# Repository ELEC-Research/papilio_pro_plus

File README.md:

# Papilio Pro Plus

This is a KICAD implementation of the Papilio Pro including production files for JLCPCB.  The Papilio pro is no longer in production so you can use this to order one for yourself.

There are some changes:
* Built-in USB-C JTAG port

## Author

Phill Brown is the primary author. 

## Licence

This work is licenced under a creative commons licence, rather like the original papilio pro.

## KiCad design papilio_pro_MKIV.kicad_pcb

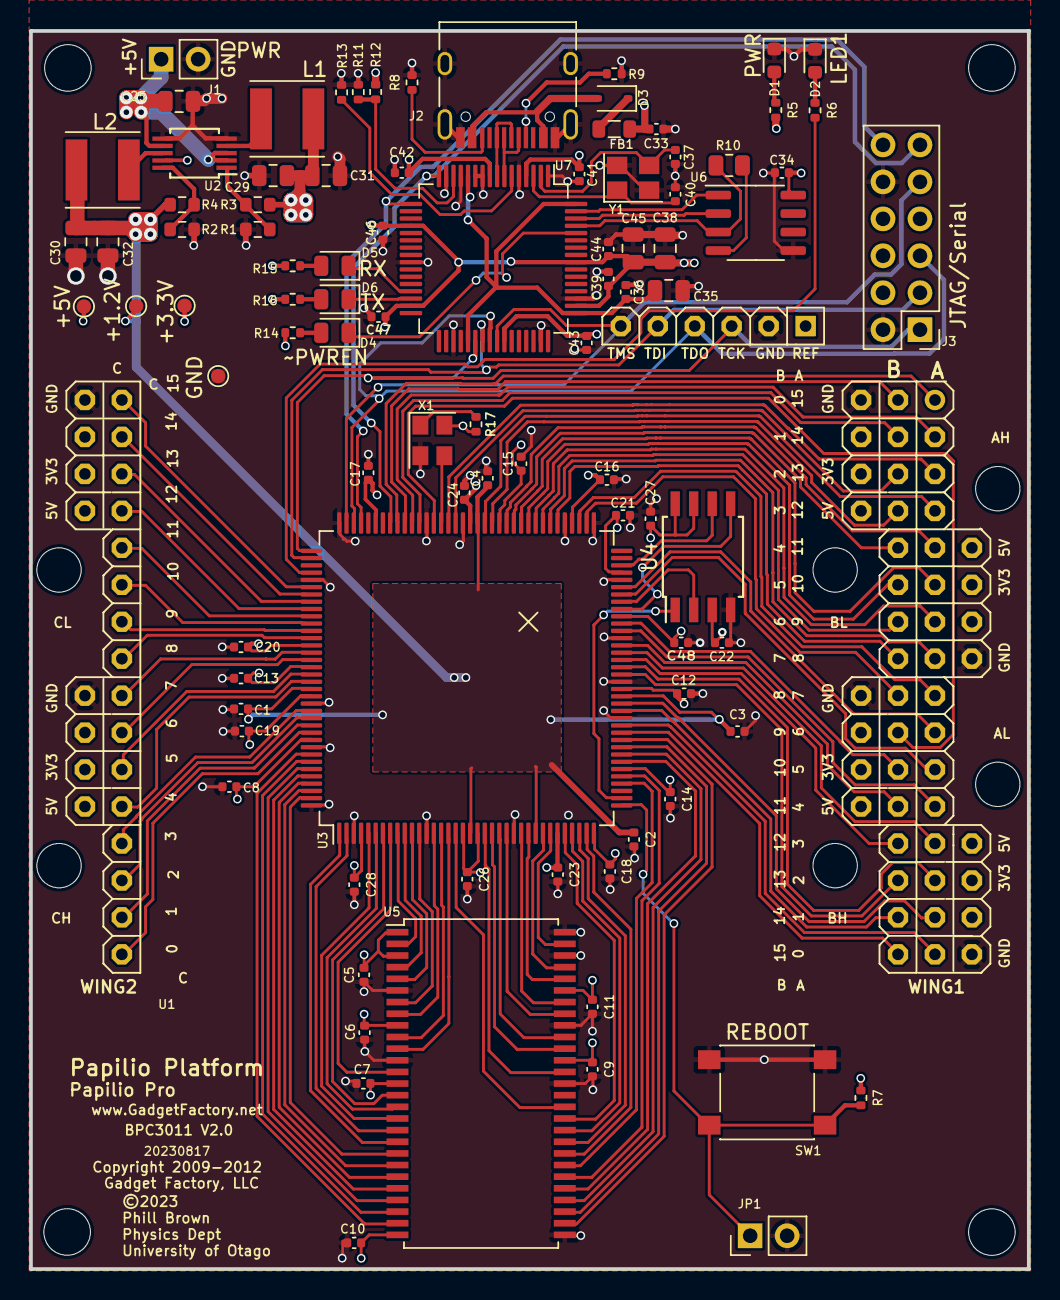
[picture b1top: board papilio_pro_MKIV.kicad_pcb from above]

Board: 4 copper layers, 68.6 x 85.1 mm, 96 parts (0 on the bottom side), 132 nets.

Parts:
C1, C2, C3, C4, C5, C6, C7, C8, C9, C10, C11, C12, C13, C14, C15, C16, C17, C18, C19, C20, C21, C22, C23, C24, C26, C27, C28, C48: .1uF; C_0402_1005Metric
C25: 10u/10V; C_0805_2012Metric
C29, C30, C31, C32: 10u/6V3; C_0805_2012Metric
C33, C34, C36, C39, C41, C42, C43, C44, C46, C47: 0.1; C_0402_1005Metric
C35: 3.3; C_0805_2012Metric
C37, C40: 27p; C_0402_1005Metric
C38, C45: 4.7; C_0805_2012Metric
D1: PWR; LED_0603_1608Metric
D2: LED1; LED_0603_1608Metric
D3: SD103AWS; D_SOD-323
D4: ~PWREN; LED_0805_2012Metric
D5: RX; LED_0805_2012Metric
D6: TX; LED_0805_2012Metric
FB1: 600 ohm; L_0805_2012Metric
H1, H2, H3, H4: MountingHole; MountingHole_3.2mm_M3
J1: PWR; PinHeader_1x02_P2.54mm_Vertical
J2: USB_C_Receptacle_USB2.0; USB_C_Receptacle_HRO_TYPE-C-31-M-12
J3: JTAG/Serial; PinHeader_2x06_P2.54mm_Vertical
JP1: JP1E; PinHeader_1x02_P2.54mm_Vertical
L1, L2: 3.3uH; L_Taiyo-Yuden_MD-5050
R1, R2, R4: 1.5K 1%; R_0603_1608Metric
R3: 6K8 1%; R_0603_1608Metric
R5: 1K8; R_0402_1005Metric
R6: 390; R_0402_1005Metric
R7: 47K; R_0402_1005Metric
R8, R9: 5.1k; R_0402_1005Metric
R10: 2.2k; R_0805_2012Metric
R11, R17: 10k; R_0402_1005Metric
R12: 4k7; R_0402_1005Metric
R13: 12k; R_0402_1005Metric
R14, R15, R16: 470; R_0402_1005Metric
SW1: REBOOT; SW_SPST_PTS645
TP1: +3.3V; TestPoint_Pad_D1.0mm
TP2: +1.2V; TestPoint_Pad_D1.0mm
TP3: +5V; TestPoint_Pad_D1.0mm
TP4: GND; TestPoint_Pad_D1.0mm
U1: Papilio Pro; COCOON_48BIT
U2: LTC3419MS; MSOP-10_3x3mm_P0.5mm
U3: XC6SLX9-TQG144; LQFP-144_20x20mm_P0.5mm
U4: 25CSM04xxSN; SOIC-8W_5.3x5.3mm_P1.27mm
U5: MT48LC16M16A2P; TSOP-II-54_22.2x10.16mm_P0.8mm
U6: 93LCxxB; SO-8_3.9x4.9mm_P1.27mm
U7: FT2232HL; LQFP-64_10x10mm_P0.5mm
X1: 3.2X2.5 32MHz Osc; Oscillator_SMD_Abracon_ASE-4Pin_3.2x2.5mm
Y1: 12MHz; Crystal_SMD_3225-4Pin_3.2x2.5mm

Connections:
+1V2: C1.1, C2.1, C3.1, C4.1, C30.1, C32.1, L2.2, R4.2, TP2.1, U3.19 (VCCINT), U3.28 (VCCINT), U3.52 (VCCINT), U3.89 (VCCINT), U3.128 (VCCINT)
+1V8: C35.1, C36.1, U7.12 (VCORE), U7.37 (VCORE), U7.49 (VREGOUT), U7.64 (VCORE)
+3.3V: C5.1, C6.1, C7.1, C8.1, C9.1, C10.1, C11.1, C12.1, C13.1, C14.1, C15.1, C16.1, C17.1, C18.1, C19.1, C20.1, C21.1, C22.1, C23.1, C24.1, C26.1, C27.1, C28.1, C29.1, C31.1, C34.1, C38.1, C39.1, C41.1, C42.1, C43.1, C44.1, C45.1, C46.1, C47.1, C48.1, J3.6, L1.2, R3.2, R7.1, R14.1, R15.1, R16.1, R17.1, TP1.1, U1.3 (3V3), U1.13 (3V3), U1.23 (3V3), U1.33 (3V3), U1.43 (3V3), U1.53 (3V3), U1.J1 (JTAG_REF), U2.9 (RUN2), U3.4 (VCCO_3), U3.18 (VCCO_3), U3.20 (VCCAUX), U3.31 (VCCO_3), U3.36 (VCCAUX), U3.42 (VCCO_2), U3.53 (VCCAUX), U3.63 (VCCO_2), U3.69 (IO_L1N_M0_CMPMISO_2), U3.76 (VCCO_1), U3.86 (VCCO_1), U3.90 (VCCAUX), U3.103 (VCCO_1), U3.122 (VCCO_0), U3.125 (VCCO_0), U3.129 (VCCAUX), U3.135 (VCCO_0), U4.3 (~WP), U4.7 (~HOLD), U4.8 (V_{CC}), U5.1 (VDD), U5.3 (VDDQ), U5.9 (VDDQ), U5.14 (VDD), U5.27 (VDD), U5.43 (VDDQ), U5.49 (VDDQ), U6.8 (VCC), U7.4 (VPHY), U7.9 (VPLL), U7.20 (VCCIO), U7.31 (VCCIO), U7.42 (VCCIO), U7.50 (VREGIN), U7.56 (VCCIO), X1.4 (Vdd)
+5V: C25.1, C33.1, FB1.1, J1.1, R5.2, R12.1, TP3.1, U1.4 (Vin), U1.14 (Vin), U1.24 (Vin), U1.34 (Vin), U1.44 (Vin), U1.54 (Vin), U2.2 (RUN1), U2.3 (MODE), U2.7 (VIN)
/Connectors/OSC_IN: U3.94 (IO_L40N_GCLK10_1), X1.3 (OUT)
/Connectors/W1_A1: U1.A0, U3.48 (IO_L48P_D7_2)
/Connectors/W1_A2: U1.A1, U3.51 (IO_L31P_GCLK31_D14_2)
/Connectors/W1_A3: U1.A2, U3.56 (IO_L30P_GCLK1_D13_2)
/Connectors/W1_A4: U1.A3, U3.58 (IO_L14P_D11_2)
/Connectors/W1_A5: U1.A4, U3.61 (IO_L12N_D2_MISO3_2)
/Connectors/W1_A6: U1.A5, U3.66 (IO_L2N_CMPMOSI_2)
/Connectors/W1_A7: U1.A6, U3.67 (IO_L2P_CMPCLK_2)
/Connectors/W1_A8: U1.A7, U3.75 (IO_L74P_AWAKE_1)
/Connectors/W1_A9: U1.A8, U3.79 (IO_L47P_1)
/Connectors/W1_A10: U1.A9, U3.81 (IO_L46P_1)
/Connectors/W1_A11: U1.A10, U3.83 (IO_L45P_1)
/Connectors/W1_A12: U1.A11, U3.85 (IO_L43P_GCLK5_1)
/Connectors/W1_A13: U1.A12, U3.88 (IO_L42P_GCLK7_1)
/Connectors/W1_A14: U1.A13, U3.93 (IO_L41P_GCLK9_IRDY1_1)
/Connectors/W1_A15: U1.A14, U3.98 (IO_L34P_1)
/Connectors/W1_A16: U1.A15, U3.100 (IO_L33P_1)
/Connectors/W1_B1: U1.B0, U3.99 (IO_L33N_1)
/Connectors/W1_B2: U1.B1, U3.97 (IO_L34N_1)
/Connectors/W1_B3: U1.B2, U3.92 (IO_L41N_GCLK8_1)
/Connectors/W1_B4: U1.B3, U3.87 (IO_L42N_GCLK6_TRDY1_1)
/Connectors/W1_B5: U1.B4, U3.84 (IO_L43N_GCLK4_1)
/Connectors/W1_B6: U1.B5, U3.82 (IO_L45N_1)
/Connectors/W1_B7: U1.B6, U3.80 (IO_L46N_1)
/Connectors/W1_B8: U1.B7, U3.78 (IO_L47N_1)
/Connectors/W1_B9: U1.B8, U3.74 (IO_L74N_DOUT_BUSY_1)
/Connectors/W1_B10: U1.B9, U3.95 (IO_L40P_GCLK11_1)
/Connectors/W1_B11: U1.B10, U3.62 (IO_L12P_D1_MISO2_2)
/Connectors/W1_B12: U1.B11, U3.59 (IO_L13N_D10_2)
/Connectors/W1_B13: U1.B12, U3.57 (IO_L14N_D12_2)
/Connectors/W1_B14: U1.B13, U3.55 (IO_L30N_GCLK0_USERCCLK_2)
/Connectors/W1_B15: U1.B14, U3.50 (IO_L31N_GCLK30_D15_2)
/Connectors/W1_B16: U1.B15, U3.47 (IO_L48N_RDWR_B_VREF_2)
/Connectors/W2_A1: U1.C15, U3.114 (IO_L65N_SCP2_0)
/Connectors/W2_A2: U1.C14, U3.115 (IO_L65P_SCP3_0)
/Connectors/W2_A3: U1.C13, U3.116 (IO_L64N_SCP4_0)
/Connectors/W2_A4: U1.C12, U3.117 (IO_L64P_SCP5_0)
/Connectors/W2_A5: U1.C11, U3.118 (IO_L63N_SCP6_0)
/Connectors/W2_A6: U1.C10, U3.119 (IO_L63P_SCP7_0)
/Connectors/W2_A7: U1.C9, U3.120 (IO_L62N_VREF_0)
/Connectors/W2_A8: U1.C8, U3.121 (IO_L62P_0)
/Connectors/W2_A9: U1.C7, U3.123 (IO_L37N_GCLK12_0)
/Connectors/W2_A10: U1.C6, U3.124 (IO_L37P_GCLK13_0)
/Connectors/W2_A11: U1.C5, U3.126 (IO_L36N_GCLK14_0)
/Connectors/W2_A12: U1.C4, U3.127 (IO_L36P_GCLK15_0)
/Connectors/W2_A13: U1.C3, U3.131 (IO_L35N_GCLK16_0)
/Connectors/W2_A14: U1.C2, U3.132 (IO_L35P_GCLK17_0)
/Connectors/W2_A15: U1.C1, U3.133 (IO_L34N_GCLK18_0)
/Connectors/W2_A16: U1.C0, U3.134 (IO_L34P_GCLK19_0)
/FPGA/A0: U3.140 (IO_L3P_0), U5.23 (A0)
/FPGA/A1: U3.139 (IO_L3N_0), U5.24 (A1)
/FPGA/A2: U3.138 (IO_L4P_0), U5.25 (A2)
/FPGA/A3: U3.137 (IO_L4N_0), U5.26 (A3)
/FPGA/A4: U3.46 (IO_L49P_D3_2), U5.29 (A4)
/FPGA/A5: U3.45 (IO_L49N_D4_2), U5.30 (A5)
/FPGA/A6: U3.44 (IO_L62P_D5_2), U5.31 (A6)
/FPGA/A7: U3.43 (IO_L62N_D6_2), U5.32 (A7)
/FPGA/A8: U3.41 (IO_L64P_D8_2), U5.33 (A8)
/FPGA/A9: U3.40 (IO_L64N_D9_2), U5.34 (A9)
/FPGA/A10: U3.141 (IO_L2N_0), U5.22 (A10)
/FPGA/A11: U3.35 (IO_L1P_3), U5.35 (A11)
/FPGA/A12: U3.34 (IO_L1N_VREF_3), U5.36 (A12)
/FPGA/BA0: U3.143 (IO_L1N_VREF_0), U5.20 (BA0)
/FPGA/BA1: U3.142 (IO_L2P_0), U5.21 (BA1)
/FPGA/CKE: U3.33 (IO_L2P_3), U5.37 (CKE)
/FPGA/CLK: U3.32 (IO_L2N_3), U5.38 (CLK)
/FPGA/CS: U3.1 (IO_L83N_VREF_3), U5.19 (~CS)
/FPGA/DQ0: U3.9 (IO_L50N_3), U5.2 (DQ0)
/FPGA/DQ1: U3.10 (IO_L50P_3), U5.4 (DQ1)
/FPGA/DQ2: U3.11 (IO_L49N_3), U5.5 (DQ2)
/FPGA/DQ3: U3.12 (IO_L49P_3), U5.7 (DQ3)
/FPGA/DQ4: U3.14 (IO_L44N_GCLK20_3), U5.8 (DQ4)
/FPGA/DQ5: U3.15 (IO_L44P_GCLK21_3), U5.10 (DQ5)
/FPGA/DQ6: U3.16 (IO_L43N_GCLK22_IRDY2_3), U5.11 (DQ6)
/FPGA/DQ7: U3.8 (IO_L51P_3), U5.13 (DQ7)
/FPGA/DQ8: U3.21 (IO_L42N_GCLK24_3), U5.42 (DQ8)
/FPGA/DQ9: U3.22 (IO_L42P_GCLK25_TRDY2_3), U5.44 (DQ9)
/FPGA/DQ10: U3.23 (IO_L41N_GCLK26_3), U5.45 (DQ10)
/FPGA/DQ11: U3.24 (IO_L41P_GCLK27_3), U5.47 (DQ11)
/FPGA/DQ12: U3.26 (IO_L37N_3), U5.48 (DQ12)
/FPGA/DQ13: U3.27 (IO_L37P_3), U5.50 (DQ13)
/FPGA/DQ14: U3.29 (IO_L36N_3), U5.51 (DQ14)
/FPGA/DQ15: U3.30 (IO_L36P_3), U5.53 (DQ15)
/FPGA/DQMH: U3.17 (IO_L43P_GCLK23_3), U5.39 (DQMH)
/FPGA/DQML: U3.7 (IO_L51N_3), U5.15 (DQML)
/FPGA/FLASH_CS: U3.38 (IO_L65N_CSO_B_2), U4.1 (~CS)
/FPGA/FLASH_SCK: U3.70 (IO_L1P_CCLK_2), U4.6 (SCK)
/FPGA/FLASH_SI: U3.64 (IO_L3N_MOSI_CSI_B_MISO0_2), U4.5 (SI)
/FPGA/FLASH_SO: U3.65 (IO_L3P_D0_DIN_MISO_MISO1_2), U4.2 (SO)
/FPGA/FPGA-C/REBOOT: JP1.1, R7.2, SW1.1, U3.37 (PROGRAM_B_2)
/FPGA/~CAS: U3.5 (IO_L52N_3), U5.17 (~CAS)
/FPGA/~RAS: U3.2 (IO_L83P_3), U5.18 (~RAS)
/FPGA/~WE: U3.6 (IO_L52P_3), U5.16 (~WE)
/USB JTAG/RXD2: J3.12, U3.105 (IO_L1P_1), U7.17 (ADBUS1)
/USB JTAG/TCK: J3.1, U1.J3 (JTAG_TCK), U3.109 (TCK), U7.38 (BDBUS0)
/USB JTAG/TDI: J3.3, U1.J5 (JTAG_TDI), U3.110 (TDI), U7.39 (BDBUS1)
/USB JTAG/TDO: J3.5, U1.J4 (JTAG_TDO), U3.106 (TDO), U7.40 (BDBUS2)
/USB JTAG/TMS: J3.9, U1.J6 (JTAG_TMS), U3.107 (TMS), U7.41 (BDBUS3)
/USB JTAG/TXD2: J3.11, U3.101 (IO_L32N_1), U7.16 (ADBUS0)
GND: C1.2, C2.2, C3.2, C4.2, C5.2, C6.2, C7.2, C8.2, C9.2, C10.2, C11.2, C12.2, C13.2, C14.2, C15.2, C16.2, C17.2, C18.2, C19.2, C20.2, C21.2, C22.2, C23.2, C24.2, C25.2, C26.2, C27.2, C28.2, C29.2, C30.2, C31.2, C32.2, C33.2, C34.2, C35.2, C36.2, C37.2, C38.2, C39.2, C40.2, C41.2, C42.2, C43.2, C44.2, C45.2, C46.2, C47.2, C48.2, D1.1 (K), D2.1 (K), J1.2, J2.A1 (GND), J2.A12 (GND), J2.B1 (GND), J2.B12 (GND), J2.S1 (SHIELD), J3.2, J3.10, JP1.2, R1.1, R2.1, R8.2, R9.2, R11.2, R13.2, SW1.2, TP4.1, U1.1 (GND), U1.11 (GND), U1.21 (GND), U1.31 (GND), U1.41 (GND), U1.51 (GND), U1.J2 (JTAG_GND), U2.5 (GND), U2.6 (GND), U3.3 (GND), U3.13 (GND), U3.25 (GND), U3.49 (GND), U3.54 (GND), U3.60 (IO_L13P_M1_2), U3.68 (GND), U3.73 (SUSPEND), U3.77 (GND), U3.91 (GND), U3.96 (GND), U3.108 (GND), U3.113 (GND), U3.130 (GND), U3.136 (GND), U3.144 (IO_L1P_HSWAPEN_0), U4.4 (V_{SS}), U5.6 (VSSQ), U5.12 (VSSQ), U5.28 (VSS), U5.41 (VSS), U5.46 (VSSQ), U5.52 (VSSQ), U5.54 (VSS), U6.5 (GND), U7.1 (GND), U7.5 (GND), U7.10 (AGND), U7.11 (GND), U7.13 (TEST), U7.15 (GND), U7.25 (GND), U7.35 (GND), U7.47 (GND), U7.51 (GND), X1.2 (GND), Y1.2, Y1.4
unnamed: D1.2 (A), R5.1
unnamed: D2.2 (A), R6.1
unnamed: D3.2 (A), J2.A4 (VBUS), J2.A9 (VBUS), J2.B4 (VBUS), J2.B9 (VBUS)
unnamed: D3.1 (K), FB1.2
unnamed: D4.2 (A), R14.2
unnamed: D4.1 (K), U7.60 (~PWREN)
unnamed: D5.2 (A), R15.2
unnamed: D5.1 (K), U7.29 (ACBUS3)
unnamed: D6.2 (A), R16.2
unnamed: D6.1 (K), U7.30 (ACBUS4)
unnamed: J2.A5 (CC1), R9.1
unnamed: J2.B5 (CC2), R8.1
unnamed: L1.1, U2.4 (SW1)
unnamed: L2.1, U2.8 (SW2)
unnamed: R1.2, R3.1, U2.1 (VFB1)
unnamed: R2.2, R4.1, U2.10 (VFB2)
unnamed: R6.2, U3.112 (IO_L66P_SCP1_0)
unnamed: U6.1 (CS), U7.63 (EECS)
unnamed: R10.1, U6.3 (DI), U7.61 (EEDATA)
unnamed: R10.2, U6.4 (DO)
unnamed: U6.2 (SCLK), U7.62 (EECLK)
unnamed: J2.A7 (D-), J2.B7 (D-), U7.7 (DM)
unnamed: J2.A6 (D+), J2.B6 (D+), U7.8 (DP)
unnamed: C37.1, U7.2 (OSCI), Y1.3
unnamed: C40.1, U7.3 (OSCO), Y1.1
unnamed: R13.1, U7.6 (REF)
unnamed: R11.1, R12.2, U7.14 (~RESET)
unnamed: R17.2, X1.1 (EN)

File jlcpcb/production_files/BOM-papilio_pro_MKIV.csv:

Comment,Designator,Footprint,LCSC
4k7,R12,R_0402_1005Metric,C105870
600 ohm,FB1,L_0805_2012Metric,C111240
6K8 1%,R3,R_0603_1608Metric,C114632
10k,R11,R_0402_1005Metric,C11616
1K8,R5,R_0402_1005Metric,C137909
.1uF,"C1,C10,C11,C12,C13,C14,C15,C16,C17,C18,C19,C2,C20,C21,C22,C23,C24,C26,C27,C28,C3,C33,C34,C36,C39,C4,C41,C42,C43,C44,C46,C47,C48,C5,C6,C7,C8,C9",C_0402_1005Metric,C1525
27p,"C37,C40",C_0402_1005Metric,C1557
10u/10V,"C25,C29,C30,C31,C32",C_0805_2012Metric,C15850
USB_C_Receptacle_USB2.0,J2,USB_C_Receptacle_HRO_TYPE-C-31-M-12,C165948
3.3,"C35,C38,C45",C_0805_2012Metric,C1779
SD103AWS,D3,D_SOD-323,C191023
REBOOT,SW1,SW_SPST_PTS645,C221872
1.5K 1%,"R1,R2,R4",R_0603_1608Metric,C22843
390,R6,R_0402_1005Metric,C25109
470,"R14,R15,R16",R_0402_1005Metric,C25117
47K,R7,R_0402_1005Metric,C25563
10k,R17,R_0402_1005Metric,C25744
12k,R13,R_0402_1005Metric,C25752
2.2k,R10,R_0805_2012Metric,C25879
5.1k,"R8,R9",R_0402_1005Metric,C25905
XC6SLX9-TQG144,U3,LQFP-144_20x20mm_P0.5mm,C27408
FT2232HL,U7,LQFP-64_10x10mm_P0.5mm,C27882
3.2X2.5 32MHz Osc,X1,Oscillator_SMD_Abracon_ASE-4Pin_3.2x2.5mm,C2901581
MT48LC16M16A2P,U5,TSOP-II-54_22.2x10.16mm_P0.8mm,C41881
93LCxxB,U6,SO-8_3.9x4.9mm_P1.27mm,C6164
LTC3419MS,U2,MSOP-10_3x3mm_P0.5mm,C684754
3.3uH,"L1,L2",L_Taiyo-Yuden_MD-5050,C703751
PWR,"D1,D2",LED_0603_1608Metric,C72043
25CSM04xxSN,U4,SOIC-8W_5.3x5.3mm_P1.27mm,C82344
~PWREN,"D4,D5,D6",LED_0805_2012Metric,C84256
12MHz,Y1,Crystal_SMD_3225-4Pin_3.2x2.5mm,C9002

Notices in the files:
papilio_pro_MKIV.kicad_pcb:
Copyright 2009-2012
©2023
